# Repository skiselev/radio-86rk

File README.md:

# Radio 86RK
Re-make of the Soviet Ham Radio computer published in Radio Magazine in 1986

## Hardware Documentation

## Table of Content
* [Introduction](#introduction)
* [Specifications](#specifications)
* [Project Notes](#project-notes)
* [Hardware Documentation](#hardware-documentation)
  * [Schematic and PCB Layout](#schematic-and-pcb-layout)
  * [Connectors](#connectors)
  * [Bill of Materials](#bill-of-materials)
  * [Memory Map](#memory-map)
* [Firmware Documentation](#firmware-documentation)
  * [Monitor](#monitor)
* [Release Notes](#release-notes)
  * [Changes](#changes)
  * [Known Issues](#known-issues)

## Introduction
This project is a remake of [Radio-86RK](https://en.wikipedia.org/wiki/Radio-86RK) - a soviet ham radio computer. The original design was published in Radio Magazine, an amateur radio and DIY electronics oriented publication, starting from [April 1986](Radio-86RK_Publications.md). Hence the "Radio" and "86" in the name ("RK" stands for ham radio computer).

The goal of the original design was to create a computer that can be built relatively easily and cheaply using commonly available components. Therefore it included several short-cuts. For example it didn't use 8228 bus controller. Instead, it uses */WR* and *DBIN* CPU signals instead to distinguish between write and read CPU cycles. Since the system doesn't decode I/O control signals, all the I/O devices are memory mapped. Another optimization is the use of DMA controller for both supplying the data to the CRT controller and for refreshing DRAMs. The system didn't support interrupts. The sound was implemented using *INTE* output of the CPU. The software would use **EI**/**DI** instructions to generate sound. There are no graphics capabilities. The font size was limited to 128 characters (8275 CRT controller limitation), and given that it had to support both Latin and Cyrillic ABCs, it only had capital letters for both ABCs. The CRT controller shares 16 MHz clock oscillator with the CPU (not uncommon in other home computers at that time period).

Despite the limitations, the design was fairly successful, many people have built this computer, and there are some that still building one, this project included. In addtion, several factories manufactured computers based on (but not always compatible with) this design - e.g. [Mikrosha](https://oldcomputer.info/8bit/mikrosha/index.htm), [Apogee BK-01](https://ru.wikipedia.org/wiki/%D0%90%D0%BF%D0%BE%D0%B3%D0%B5%D0%B9_%D0%91%D0%9A-01), and a few more.

### Specifications of the Original Design
  * KR580VM80A (Intel 8080) CPU @ 1.78 MHz (16 MHz divided by 9)
  * 16 KiB to 32 KiB DRAM, 2 KiB ROM (monitor software)
  * KR580VG75 (Intel 8275) CRT controller which works together with KR580VT57 (Intel 8257) DMA controller. 1 KiB ROM is used for font
  * Two KR580VV55A (Intel 8255A) PPIs. One is used for keyboard and cassette I/O, another one for the extension port
  * Normally the computer consisted of 2 or 3 PCBs - the mainboard, the keyboard, and the keypad.

### Modifications to the Original Design
 * 16 DRAM ICs replaced with a single 32 KiB SRAM IC
 * Font ROM size increased to 2 KiB, so that it fits an alternative font. CRT controller GPA0 attribute is used to switch between fonts.
 * Reverse video attribute implemented in CRT controller
 * Added 8251 USART and 8253 timer. The timer is used for dividing the clock for USART and for sound generation.
 * Single board design, including an integrated mechanical keyboard
 * The work is largely based on [Radio-86RК-SRAM](http://radio86rk.pbworks.com/w/page/58467718/Radio-86R%D0%9A-SRAM) project created by Alexey Khudyakov (alexcp).

## Specifications
* Processor: Intel 8080A / КР580ВМ80А CPU running at 1.78 MHz
* Memory:
  * RAM: 32 KiB SRAM
  * ROM: 2 KiB UV EPROM with system monitor software
* Video: Intel 8275 / КР580ВГ75 CRT Controller
  * Alphanumeric display
  * 2 KiB UV EPROM with font
  * Composite video output (50 Hz)
* Audio:
  * Intel 8253 / КР580ВИ53 (single channel)
  * CPU INTE output
* Parallel Interface:
  * Intel 8255А / КР580ВВ55А PPI
  * 26-pin expansion header
* Serial Interface:
  * Intel 8251А / КР580ВВ51А USART
  * DE-9 connector
* Built-in 67-keys keyboard
* Cassette recorder interface

## Project Notes

Check [Project Notes](Project_Notes.md) for the information about building this project

## Hardware Documentation

### Documentation for the Previous Versions

* [Version 1.3](https://github.com/skiselev/radio-86rk/tree/v1.3)
* [Version 1.2](https://github.com/skiselev/radio-86rk/tree/v1.2)
* [Version 1.1](https://github.com/skiselev/radio-86rk/tree/v1.1)

### Schematic and PCB Layout

* [Schematic - Version 1.4](KiCad/Radio-86RK-Schematic-1.4.pdf)
* [PCB Layout - Version 1.4](KiCad/Radio-86RK-Board-1.4.pdf)

### Connectors

#### J1 - Composite Video

Pin | Description     
--- | ---------------
Tip (the inner contact) | Output: Composite Video
Ring / Sleeve         |	Power: GND

#### J2 - Power (5V)
Connect regulated +5V power supply to this connector.

Note: The 8080A CPU, clock generator, and serial port transmitters and receivers use +12V/-5V/-12V voltages. An on-board DC-DC converter (U26) is used to obtain these voltages. Instead of using the DC-DC converter it is possible to provide these voltages directly to the system using J3 connector.

Pin | Description     
--- | ---------------
Tip (the inner contact) | Power: 5V (positive terminal)
Barrel / Sleeve         |	Power: GND (negative terminal)

#### J3 - Power (5V, 12V, -12V)
Connect regulated 5V/12V/-12V power supply to this connector.

Pin | Description     
--- | ---------------
1, 2, 3 | Power: GND
4, 5, 6 |	Power: 5V
7   |	Power: 12V
8   |	Power: -12V

#### J4 - Cassette Connector
Pin | Description     
--- | ---------------
1, 2, 3, 8   | Power: GND
4   |	Output: Sound output to cassette recorder (line level)
5   |	Input: Sound input from cassette recorder (line level)
6, 7 |	Not connected

#### J5 - Serial Port Connector
Pin | Description     
--- | ---------------
1   | Not connected: DCD
2   | Input: RX
3   | Output: TX
4   | Output: DTR
5   | Power: GND
6   | Input: DSR
7   | Output: RTS
8   | Input: CTS
9   | Not connected: RI

#### J6 - Parallel Port Connector
Pin | Description | Pin | Description
--- | ----------- | --- | ----------------
1   | Output: PC0 | 2   | Input: PA0
3   | Output: PC1 | 4   | Input: PA1
5   | Output: PC2 | 6   | Input: PA2
7   | Output: PC3 | 8   | Input: PA3
9   | Output: PC4 | 10  | Input: PA4
11  | Output: PC5 | 12  | Input: PA5
13  | Output: PC6 | 14  | Input: PA6
15  | Output: PC7 | 16  | Input: PA7
17  | Output: PB7 | 18  | Output: PB0
19  | Output: PB6 | 20  | Output: PB1
21  | Output: PB5 | 22  | Output: PB2
23  | Output: PB4 | 24  | Output: PB3
25  | Power: +5V  | 26  | Power: GND

### Bill of Materials

* [Radio-86RK project on Mouser.com](https://www.mouser.com/ProjectManager/ProjectDetail.aspx?AccessID=d3d8f92a02) - View and order all components except of the PCB, and most Intel 8xxx ICs.

* [Unicorn Electronics](https://www.unicornelectronics.com/prod.htm) is a good source for Intel 8xxx or compatible ICs, 7400-series TTL ICs, and 74LS00-series TTL-LS ICs

Component type     | Reference | Description                                 | Quantity | Possible sources and notes
------------------ | --------- | ------------------------------------------- | -------- | --------------------------
PCB                |           | Radio-86RK PCB                              | 1        | Buy from my Tindie store: [Radio-86RK - PCB](https://www.tindie.com/products/weird/radio-86rk-pcb/) or order from a PCB manufacturer of your choice using provided Gerber or KiCad files
Capacitor          | C1 - C32  | 0.1 uF, MLCC, 5 mm Pitch                    | 32       | Mouser [594-K104K15X7RF53H5](https://www.mouser.com/ProductDetail/594-K104K15X7RF53H5)
Capacitor          | C33 - C38 | 47 uF, 25V, Electrolytic or Organic Polymer | 6 	      | Mouser [80-A750EK476M1EAAE40](https://www.mouser.com/ProductDetail/80-A750EK476M1EAAE40)
Capacitor          | C39       | 0.22 uF, MLCC, 5 mm Pitch                   | 1        | Mouser [810-FG24X7R1H224KNT0](https://www.mouser.com/ProductDetail/810-FG24X7R1H224KNT0)
Capacitor          | C40       | 22 nF, MLCC, 5 mm Pitch                     | 1        | Mouser [810-FG28X7R1H223KNT0](https://www.mouser.com/ProductDetail/810-FG28X7R1H223KNT0)
Capacitor          | C41       | 10 nF, MLCC, 5 mm Pitch                     | 1        | Mouser [810-FG28X7R1H103KNT0](https://www.mouser.com/ProductDetail/810-FG28X7R1H103KNT0)
Capacitor          | C42       | 2.2 nF, MLCC, 5 mm Pitch                    | 1        | Mouser [810-FG28X7R1H222KNT0](https://www.mouser.com/ProductDetail/810-FG28X7R1H222KNT0)
Capacitor          | C43       | 1 nF, MLCC, 5 mm Pitch                      | 1        | Mouser [810-FG28C0G1H102JNT6](https://www.mouser.com/ProductDetail/810-FG28C0G1H102JNT6)
Capacitor          | C44       | 10 pF, MLCC, 5 mm Pitch                     | 1        | Mouser [810-FG28C0G1H100DNT00](https://www.mouser.com/ProductDetail/810-FG28C0G1H100DNT0)
Diode              | D1 - D9  | 1N4148                                       | 9        | Mouser [512-1N4148](https://www.mouser.com/ProductDetail/512-1N4148)
LED                | D10       | LED Indicator, 3 mm, Green                  | 1        | Mouser [630-HLMP-1503-C0002](https://www.mouser.com/ProductDetail/630-HLMP-1503-C0002)
LED                | D11       | LED Indicator, 3 mm, Yellow                 | 1        | Mouser [630-HLMP-1401](https://www.mouser.com/ProductDetail/630-HLMP-1401)
Polyfuse           | F1        | 1.1A, 5 mm Pitch                            | 1        | Mouser [576-16R110BU](https://www.mouser.com/ProductDetail/576-16R110BU)
Connector          | JP1, JP2  | 4 pin header, 2.54 mm Pitch                 | 2        | Mouser [649-68000-204HLF](https://www.mouser.com/ProductDetail/649-68000-204HLF)
Connector          | JP1, JP2  | Jumper, 2.54 mm Pitch                       | 4        | Mouser [806-SX1100-B)](https://www.mouser.com/ProductDetail/806-SX1100-B)
Connector          | J1        | RCA Phono connector, Yellow                 | 1        | Mouser [490-RCJ-014](https://www.mouser.com/ProductDetail/490-RCJ-014)
Connector          | J2        | DC Power Jack, 2mm                          | 1        | Mouser [806-KLDX-0202-A](https://www.mouser.com/ProductDetail/806-KLDX-0202-A)
Connector          | J3        | 8 pin friction lock connector               | 1        | Mouser [571-6404568](https://www.mouser.com/ProductDetail/571-6404568)
Connector          | J4        | DIN 8-pos, Right Angle, PCB mount           | 1        | Mouser [490-SDF-80J](https://www.mouser.com/ProductDetail/490-SDF-80J)
Connector          | J5        | Sub-D DE9M, Right Angle, PCB mount          | 1        | Mouser [523-L717SDE09P1ACH3R](https://www.mouser.com/ProductDetail/523-L717SDE09P1ACH3R)
Connector          | J6        | 13x2 pin header, shrouded                   | 1        | Mouser [517-30326-6002](https://www.mouser.com/ProductDetail/517-30326-6002)
Connector          | J7        | 20x1 pin socket                             | 1        | Mouser [517-929850-01-20-RB](https://www.mouser.com/ProductDetail/517-929850-01-20-RB). Note: Optional, for extension board connection
Transistor         | Q1, Q2    | 2N3904                                      | 2        | Mouser [512-2N3904TA](https://www.mouser.com/ProductDetail/512-2N3904TA)
Resistor           | R1        | 33 ohm                                      | 1        | Mouser [660-CF1/4CT52R330J](https://www.mouser.com/ProductDetail/660-CF1-4CT52R330J)
Resistor           | R2        | 75 ohm                                      | 1        | Mouser [660-CF1/4CT52R750J](https://www.mouser.com/ProductDetail/660-CF1-4CT52R750J)
Resistor           | R3        | 150 ohm                                     | 1        | Mouser [660-CF1/4CT52R151J](https://www.mouser.com/ProductDetail/660-CF1-4CT52R151J)
Resistor           | R4        | 330 ohm                                     | 1        | Mouser [660-CF1/4CT52R331J](https://www.mouser.com/ProductDetail/660-CF1-4CT52R331J)
Resistor           | R5        | 1.5 k                                       | 1        | Mouser [660-CF1/4CT52R152J](https://www.mouser.com/ProductDetail/660-CF1-4CT52R152J)
Resistor           | R6 - R13  | 1 k                                         | 8        | Mouser [660-CF1/4CT52R102J](https://www.mouser.com/ProductDetail/660-CF1-4CT52R102J)
Resistor           | R14       | 2.4 k                                       | 1        | Mouser [660-CF1/4CT52R242J](https://www.mouser.com/ProductDetail/660-CF1-4CT52R242J)
Resistor           | R15       | 12 k                                        | 1        | Mouser [660-CF1/4CT52R123J](https://www.mouser.com/ProductDetail/660-CF1-4CT52R123J)
Resistor Array     | RN1       | 10 k, SIP10                                 | 1        | Mouser [652-4610X-1LF-10K](https://www.mouser.com/ProductDetail/652-4610X-1LF-10K)
Resistor Array     | RN2 - RN4 | 4.7 k, SIP6                                 | 3        | Mouser [652-4606X-1LF-4.7K](https://www.mouser.com/ProductDetail/652-4606X-1LF-4.7K)
Speaker            | SP1       | 12 mm speaker                               | 1        | Mouser [665-AT-1224TWTR](https://www.mouser.com/ProductDetail/665-AT-1224TWTR)
Keyboard Switch    | SW1 - SW67 | Cherry MX Blue (Clicky)                    | 67       | Mouser [540-MX1A-E1NW](https://www.mouser.com/ProductDetail/540-MX1A-E1NW)
Switch Leveling Kit | SW11, SW64 | Leveling kit for MX 1x2, 1x2.25, 1x2.75   | 2        | Mouser [540-G99-0742](https://www.mouser.com/ProductDetail/540-G99-0742)
Switch Leveling Kit | SW64     | Leveling kit for MX 1x8                     | 1        | Mouser [540-G99-0226](https://www.mouser.com/ProductDetail/540-G99-0226) Note: Use the wire from this part and one of 540-G99-0742 to build a through hole leveling kit for the spacebar
Tactile Switch     | SW68      | 6 mm Tactile Switch Right Angle             | 1        | Mouser [653-B3F-3152](https://www.mouser.com/ProductDetail/653-B3F-3152)
Switch Keycap      | SW68      | 4 x 4 mmm Tactile Switch Key Cap, Orange    | 1        | Mouser [653-B32-1020](https://www.mouser.com/ProductDetail/653-B32-1020)
Integrated Circuit | U1        | Intel 8080A / КР580ВМ80А, CPU               | 1        | Unicorn Electronics [8080A](https://www.unicornelectronics.com/IC/8000.html), Jameco [52046](https://www.jameco.com/z/8080A-Major-Brands-IC-8080A-8-Bit-MOS-MPU_52046.html)
Integrated Circuit | U2        | Intel 8224 / КР580ГФ24, Clock Generator     | 1        | Unicorn Electronics [8224](https://www.unicornelectronics.com/IC/8000.html)
Integrated Circuit | U3        | Intel 8251А / КР580ВВ51А, USART             | 1        | Unicorn Electronics [8251A](https://www.unicornelectronics.com/IC/8000.html)
Integrated Circuit | U4        | Intel 8253 / КР580ВИ53, PIT                 | 1        | Unicorn Electronics [8253](https://www.unicornelectronics.com/IC/8000.html), Mouser [968-CP82C54Z](https://www.mouser.com/ProductDetail/968-CP82C54Z)
Integrated Circuit | U5, U6    | Intel 8255А / КР580ВВ55А, PPI               | 2        | Unicorn Electronics [8055A](https://www.unicornelectronics.com/IC/8000.html), Mouser [968-CP82C55A-5Z](https://www.mouser.com/ProductDetail/968-CP82C55A-5Z), Jameco [52732](https://www.jameco.com/z/8255A-5-Major-Brands-IC-8255A-5-Programmable-Peripheral-Interface-40-pin-DIP_52732.html)
Integrated Circuit | U7        | Intel 8257 / КР580ВТ57, DMA Controller      | 1        | Unicorn Electronics [8257](https://www.unicornelectronics.com/IC/8000.html)
Integrated Circuit | U8        | Intel 8275 / КР580ВГ75, CRT Controller      | 1        | Unicorn Electronics [8275](https://www.unicornelectronics.com/IC/8000.html), Jameco [52821](https://www.jameco.com/z/8275-Major-Brands-Programmable-CRT-Controller-DIP-40_52821.html)
Integrated Circuit | U9        | AS6C62256, SRAM 32Kx8                       | 1        | Mouser [913-AS6C62256-55PCN](https://www.mouser.com/ProductDetail/913-AS6C62256-55PCN), Unicorn Electronics [62256LP](https://www.unicornelectronics.com/IC/STATIC.html)
Integrated Circuit | U10, U11  | 2716 / КР573РФ5, 2Kx8 EPROM                 | 2        | Mouser [556-AT28C64B15PU](https://www.mouser.com/ProductDetail/556-AT28C64B15PU), Unicorn Electronics [2716](https://www.unicornelectronics.com/IC/EPROM.html). Note: 2716, 2732, 2764, 27C64 EPROMs, or 28C64 EEPROMs can be used
Integrated Circuit | U12       | 74LS373/К555ИР22, 8-bit Latch, 3-state outputs | 1     | Mouser [595-SN74LS373N](https://www.mouser.com/ProductDetail/595-SN74LS373N)
Integrated Circuit | U13       | 74198/К155ИР13, 8-bit Shift Register        | 1        | Unicorn Electronics [74198](https://www.unicornelectronics.com/IC/7400.html)
Integrated Circuit | U14       | 74LS138/К555ИД7, Decoder 3 to 8 active low outputs | 1 | Mouser [595-SN74LS138N](https://www.mouser.com/ProductDetail/595-SN74LS138N), Unicorn Electronics [74LS138](https://www.unicornelectronics.com/IC/74LS.html)
Integrated Circuit | U15       | 7492/К155ИЕ4, Divide by 12 counter          | 1        | Mouser [595-SN74LS92N](https://www.mouser.com/ProductDetail/595-SN74LS92N), Unicorn Electronics [74LS92](https://www.unicornelectronics.com/IC/74LS.html)
Integrated Circuit | U16       | 7486/К155ЛП5, Quad 2-input XOR              | 1        | Mouser [595-SN74LS86AN](https://www.mouser.com/ProductDetail/595-SN74LS86AN), Unicorn Electronics [74LS86](https://www.unicornelectronics.com/IC/74LS.html)
Integrated Circuit | U17       | 7474/К155ТМ2, Dual D Flip-flop, Set & Reset | 1        | Mouser [595-SN74LS74AN](https://www.mouser.com/ProductDetail/595-SN74LS74AN), Unicorn Electronics [74LS74](https://www.unicornelectronics.com/IC/74LS.html)
Integrated Circuit | U18       | 7408/К155ЛИ1, Quad 2-input AND              | 1        | Mouser [595-SN74LS08N](https://www.mouser.com/ProductDetail/595-SN74LS08N), Unicorn Electronics [74LS08](https://www.unicornelectronics.com/IC/74LS.html)
Integrated Circuit | U19       | 7404/К155ЛН1, Hex Inverter                  | 1        | Mouser [595-SN74LS04N](https://www.mouser.com/ProductDetail/595-SN74LS04N), Unicorn Electronics [74LS04](https://www.unicornelectronics.com/IC/74LS.html)
Integrated Circuit | U20       | 7400/К155ЛА3, Quad 2-input NAND             | 1        | Mouser [595-SN74LS00N](https://www.mouser.com/ProductDetail/595-SN74LS00N), Unicorn Electronics [74LS00](https://www.unicornelectronics.com/IC/74LS.html)
Integrated Circuit | U21       | TL071/К140УД6, Operational Amplifier        | 1        | Mouser [595-TL071IP](https://www.mouser.com/ProductDetail/595-TL071IP)
Integrated Circuit | U22       | SN75154N/К170УП2В, Quad RS-232 Receiver     | 1        | Mouser [595-SN75154N](https://www.mouser.com/ProductDetail/595-SN75154N), Unicorn Electronics [75154](https://www.unicornelectronics.com/IC/INTERFACE.html)
Integrated Circuit | U23, U24  | SN75150P/К170АП2, Dual RS-232 Driver        | 2        | Mouser [595-SN75150P](https://www.mouser.com/ProductDetail/595-SN75150P), Unicorn Electronics [75150](https://www.unicornelectronics.com/IC/INTERFACE.html)
Integrated Circuit | U25       | LM7905/КР1179ЕНВ, Negative 5V 1A Linear Regulator | 1  | Mouser [926-LM7905CT-NOPB](https://www.mouser.com/ProductDetail/926-LM7905CT-NOPB), Unicorn Electronics [7905T](https://www.unicornelectronics.com/IC/VOLT.html)
DC-DC Converter    | U26       | IZ0512, +/-12V +/-125mA, 4.5V-9V input      | 1        | Mouser [209-IZ0512S](https://www.mouser.com/ProductDetail/209-IZ0512S)
Integrated Circuit | U27       | DS1233-5, CPU Supervisory Circuit           | 1        | Mouser [700-DS1233-5T&R](https://www.mouser.com/ProductDetail/700-DS1233-5TR)
Crystal            | Y1        | 16 MHz, Series, HC-49U                      | 1        | Mouser [774-ATS160-E](https://www.mouser.com/ProductDetail/774-ATS160-E)
IC Socket          | U1, U5, U6, U7, U8 | 40 pin DIP                         | 5        | Mouser [649-DILB40P223TLF](https://www.mouser.com/ProductDetail/649-DILB40P223TLF), [517-4840-6000-CP](https://www.mouser.com/ProductDetail/517-4840-6000-CP)
IC Socket          | U3, U9, U10, U11    | 28 pin DIP                                  | 4        | Mouser [649-DILB28P223TLF](https://www.mouser.com/ProductDetail/649-DILB28P223TLF), [517-4828-6000-CP](https://www.mouser.com/ProductDetail/517-4828-6000-CP)
IC Socket          | U4, U13   | 24 pin DIP                          | 2        | Mouser [649-DILB24P-223TLF](https://www.mouser.com/ProductDetail/649-DILB24P-223TLF), [517-4824-6000-CP](https://www.mouser.com/ProductDetail/517-4824-6000-CP)
IC Socket          | U12       | 20 pin DIP                                  | 1        | Mouser [649-DILB20P-223TLF](https://www.mouser.com/ProductDetail/649-DILB20P-223TLF), [517-4820-3000-CP](https://www.mouser.com/ProductDetail/517-4820-3000-CP)
IC Socket          | U2, U14, U22 | 16 pin DIP                               | 3        | Mouser [649-DILB16P-223TLF](https://www.mouser.com/ProductDetail/649-DILB16P-223TLF), [517-4816-3000-CP](https://www.mouser.com/ProductDetail/517-4816-3000-CP)
IC Socket          | U15 - U20 | 14 pin DIP                                  | 6        | Mouser [649-DILB14P-223TLF](https://www.mouser.com/ProductDetail/649-DILB14P-223TLF), [517-4814-3000-CP](https://www.mouser.com/ProductDetail/517-4814-3000-CP)
IC Socket          | U21, U23, U24 | 8 pin DIP                               | 3        | Mouser [649-DILB8P223TLF](https://www.mouser.com/ProductDetail/649-DILB8P223TLF), [517-4808-3000-CP](https://www.mouser.com/ProductDetail/517-4808-3000-CP)

### Memory Map
* 0000h - 7FFFh - SRAM
  * 7600h - 7FFFh - Display buffer and monitor variables
* 8000h - 8FFFh - 8255A PPI (Keyboard, Cassette recorder, Sound control)
  * 8000h - Channel A data
  * 8001h - Channel B data
  * 8002h - Channel C data
  * 8003h - Control word
* 9000h - 9FFFh - 8253 Timer (USART Clock, Sound)
  * 9000h - Channel 0 count
  * 9001h - Channel 1 count
  * 9002h - Channel 2 count
  * 9003h - Control word
* 0A000h - 0AFFFh - 8255A PPI (Parallel Interface)
  * 0A000h - Channel A data
  * 0A001h - Channel B data
  * 0A002h - Channel C data
  * 0A003h - Control word
* 0B000h - 0BFFFh - 8251A USART
  * 0B000h - Data register
  * 0B001h - Command register
* 0C000h - 0CFFFh - 8275 CRT Controller
* 0D000h - 0DFFFh - Unused
* 0E000h - 0EFFFh - 8257 DMA Controller (write only)
* 0E000h - 0FFFFh - Monitor EPROM (read only)

## Firmware Documentation

### Monitor

#### Monitor Commands
* Memory Operations
  * **D\<Start_Address\>,\<End_Address\>** - Display memory content in hexadecimal
  * **L\<Start_Address\>,\<End_Address\>** - Display memory content in ASCII
  * **F\<Start_Address\>,\<End_Address\>,\<Value\>** - Fill memory with the specified value
  * **M\<Address\>** - Modify memory content
  * **T\<Start_Address\>,\<End_Address\>,\<Destination_Start_Address\>** - Copy memory block to destination
  * **C\<Start_Address\>,\<End_Address\>,\<Destination_Start_Address\>** - Compare memory block with destination
  * **S\<Start_Address\>,\<End_Address\>,\<Value\>** - Search memory for a value
  * **R\<ROM_Start_Address\>,\<ROM_End_Address\>,\<Destination_Start_Address\>** - Read from the ROM connected to the Parallel interface to memory
* Run Control
  * **G\<Start_Address\>\[,End_Address\]** - Run code, optionally stop at the specified address
  * **X** - Display and modify registers
* Cassette Input/Output
  * **O\<Start_Address\>,\<End_Address\>\[,Speed\]** - Write memory to cassette. Default speed is 1Dh / 1200 bps
  * **I\[Offset\]\[,Speed\]** - Read data from to cassette memory at specified offset

#### Monitor Subroutines:
* 0F803h - Keyboard input
  * Input: None
  * Output: A - character code read from keyboard
* 0F806h - Cassette input
  * Input: A=0FFh - with sync; A=08h - no sync
  * Output: A - data read from cassette
* 0F809h - Print character to screen
  * Input: C - character to print
* 0F80Ch - Cassette output
  * Input: C - data to write
* 0F812h - Query keyboard
  * Output: A=00h - key not pressed; A=0FFh - key pressed
* 0F815h - Print to screen in hex
  * Input: A - data to print
* 0F818h - Print string
  * Input: HL - string address
* 0F81Bh - Get key
  * Output: A=0FFh - key not pressed; A=0FEh - Rus/Lat; otherwise A - key code
* 0F81Eh - Get cursor position
  * Output: H - row, L - column
* 0F821h - Read character from screen at current cursor position
  * Output: A - char read from screen
* 0F824h - Read from cassette
  * Input: HL - offset of memory buffer to store data to
  * Output: HL - start; DE - end; BC - checksum

## Release Notes

### Changes
* Version 1.4
  * Change keyboard layout to QWERTY
  * Add the J7 extension connector
  * Add support for 2732, 2764 and 27C64 EPROMs and 28C64 EEPROM.

* Version 1.3
  * Fix issues from version 1.1 and version 1.2:
    * Use key labels "Ь X" and "СС SHIFT" on top silkscreen
    * Video signal generation circuit: use R2 = 75 Ohm and R5 = 1.5 kOhm
    
* Version 1.2
  * Add F5 key
  * Add copyright year on the top silkscreen

* Version 1.1
  * Fix all known issues of version 1.0
  * Use DS1233-5 mircoprocessor supervisor to generate reset signal
  * Implement reverse video attribute

* Version 1.0
  * Initial version

### Known Issues
* Version 1.3
  * No known issues

* Version 1.2
  * Top silkscreen: "Ь" and "X" key labels are swapped
  * Top silkscreen: More correct translation for "СС" is "SHIFT"
  * Video signal generation: Produced video Vpp and the backporch levels are a bit too high. Use R2 = 75 to 100 Ohm, and R5 = 1.5 kOhm for proper video signal levels (Reported by Martin Lukasek)
* Version 1.1
  * Top silkscreen: "Ь" and "X" key labels are swapped
  * Top silkscreen: More correct translation for "СС" is "SHIFT"
  * Top silkscreen: No copyright year
  * Video signal generation: Produced video Vpp and the backporch levels are a bit too high. Use R2 = 75 to 100 Ohm, and R5 = 1.5 kOhm for proper video signal levels (Reported by Martin Lukasek)

* Version 1.0
  * 8224 (U2) should use DIP-16 footprint
  * Down and Right buttons swapped
  * Reset RC does not provide enough time for the system to properly reset at power-on

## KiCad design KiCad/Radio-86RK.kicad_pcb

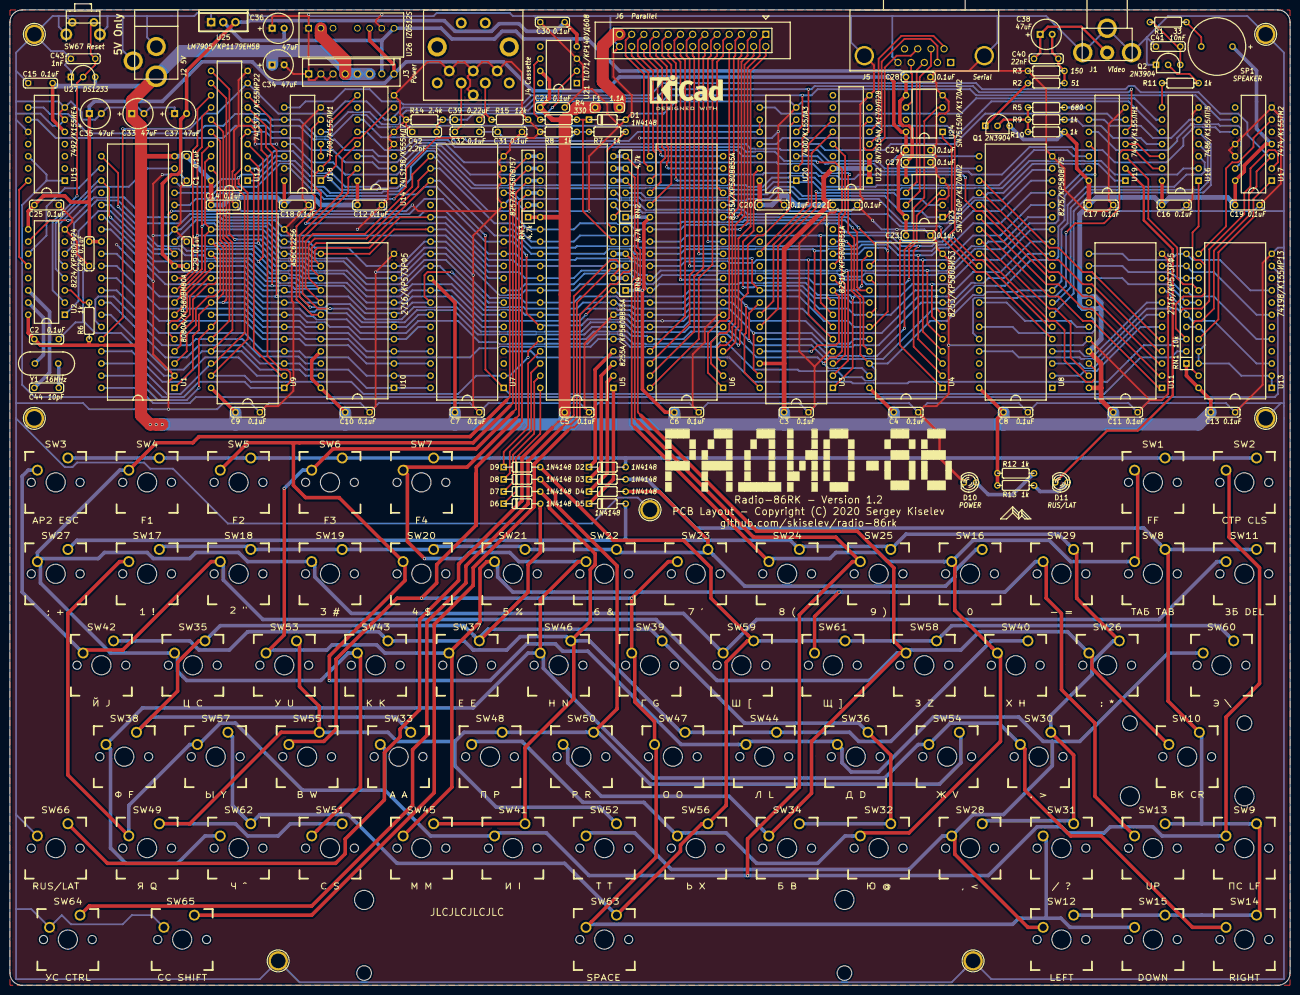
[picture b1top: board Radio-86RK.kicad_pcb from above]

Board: 2 copper layers, 266.7 x 203.2 mm, 186 parts (0 on the bottom side), 194 nets.

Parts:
C1, C2, C3, C4, C5, C6, C7, C8, C9, C10, C11, C12, C13, C14, C15, C16, C17, C18, C19, C20, C21, C22, C23, C24, C25, C26, C27, C28, C29, C30, C31, C32: 0.1uF; Cap_Cer_508
C33, C34, C35, C36, C37, C38: 47uF; Cap_Elec_Radial_6.3mm
C39: 0.22uF; Cap_Cer_508
C40: 22nF; Cap_Cer_508
C41: 10nF; Cap_Cer_508
C42: 2.2nF; Cap_Cer_508
C43: 1nF; Cap_Cer_508
C44: 10pF; Cap_Cer_508
D1, D2, D3, D4, D5, D6, D7, D8, D9: 1N4148; Diode_762
D10: POWER; LED_3mm
D11: RUS/LAT; LED_3mm
F1: 1.1A; Cap_Cer_508
HOLE1, HOLE2, HOLE3, HOLE4, HOLE5, HOLE6, HOLE7: M3; Hole_3mm
J1: Video; Conn_RCA_Right
J2: 5V; Conn_Power_Jack_Circular_Pads
J3: Power; Conn_Friction_Lock_8P_2.54mm
J4: Cassette; Conn_DIN_8pin
J5: Serial; Conn_Dsub_DE9M
J6: Parallel; Conn_Pin_Header_13x2_2.54mm_Shrouded
Q1, Q2: 2N3904; Transistor_TO92_EBC_254
R1: 33; Res_762
R2: 51; Res_762
R3: 150; Res_762
R4: 330; Res_762
R5: 680; Res_762
R6, R7, R8, R9, R10, R11, R12, R13: 1k; Res_762
R14: 2.4k; Res_762
R15: 12k; Res_762
RN1: 10k; Conn_SIL10
RN2, RN3, RN4: 4.7k; Conn_SIL6
SP1: SPEAKER; Speaker_12mm
SW1: FF; CHERRY_PCB_100H
SW2: СТР CLS; CHERRY_PCB_100H
SW3: АР2 ESC; CHERRY_PCB_100H
SW4: F1; CHERRY_PCB_100H
SW5: F2; CHERRY_PCB_100H
SW6: F3; CHERRY_PCB_100H
SW7: F4; CHERRY_PCB_100H
SW8: ТАБ TAB; CHERRY_PCB_100H
SW9: ПС LF; CHERRY_PCB_100H
SW10: ВК CR; CHERRY_PCB_225H
SW11: ЗБ DEL; CHERRY_PCB_100H
SW12: LEFT; CHERRY_PCB_100H
SW13: UP; CHERRY_PCB_100H
SW14: RIGHT; CHERRY_PCB_100H
SW15: DOWN; CHERRY_PCB_100H
SW16: 0; CHERRY_PCB_100H
SW17: 1 !; CHERRY_PCB_100H
SW18: 2 "; CHERRY_PCB_100H
SW19: 3 #; CHERRY_PCB_100H
SW20: 4 $; CHERRY_PCB_100H
SW21: 5 %; CHERRY_PCB_100H
SW22: 6 &; CHERRY_PCB_100H
SW23: 7 '; CHERRY_PCB_100H
SW24: 8 (; CHERRY_PCB_100H
SW25: 9 ); CHERRY_PCB_100H
SW26: : *; CHERRY_PCB_100H
SW27: ; +; CHERRY_PCB_100H
SW28: , <; CHERRY_PCB_100H
SW29: - =; CHERRY_PCB_100H
SW30: . >; CHERRY_PCB_100H
SW31: / ?; CHERRY_PCB_100H
SW32: Ю @; CHERRY_PCB_100H
SW33: А A; CHERRY_PCB_100H
SW34: Б B; CHERRY_PCB_100H
SW35: Ц C; CHERRY_PCB_100H
SW36: Д D; CHERRY_PCB_100H
SW37: Е E; CHERRY_PCB_100H
SW38: Ф F; CHERRY_PCB_100H
SW39: Г G; CHERRY_PCB_100H
SW40: Х H; CHERRY_PCB_100H
SW41: И I; CHERRY_PCB_100H
SW42: Й J; CHERRY_PCB_100H
SW43: К K; CHERRY_PCB_100H
SW44: Л L; CHERRY_PCB_100H
SW45: М M; CHERRY_PCB_100H
SW46: Н N; CHERRY_PCB_100H
SW47: О O; CHERRY_PCB_100H
SW48: П P; CHERRY_PCB_100H
SW49: Я Q; CHERRY_PCB_100H
SW50: Р R; CHERRY_PCB_100H
SW51: С S; CHERRY_PCB_100H
SW52: Т T; CHERRY_PCB_100H
SW53: У U; CHERRY_PCB_100H
SW54: Ж V; CHERRY_PCB_100H
SW55: В W; CHERRY_PCB_100H
SW56: Ь X; CHERRY_PCB_100H
SW57: Ы Y; CHERRY_PCB_100H
SW58: З Z; CHERRY_PCB_100H
SW59: Ш [; CHERRY_PCB_100H
SW60: Э \; CHERRY_PCB_150H
SW61: Щ ]; CHERRY_PCB_100H
SW62: Ч ^; CHERRY_PCB_100H
SW63: SPACE; CHERRY_PCB_625H
SW64: УС CTRL; CHERRY_PCB_125H
SW65: CC SHIFT; CHERRY_PCB_125H
SW66: RUS/LAT; CHERRY_PCB_100H
SW67: Reset; Switch_Tactile_6mm_Right
U1: 8080A/КР580ВМ80А; IC_DIP40_600
U2: 8224/КР580ГФ24; IC_DIP16_300
U3: 8251A/КР580ВВ51А; IC_DIP28_600
U4: 8253/КР580ВИ53; IC_DIP24_600
U5, U6: 8255A/КР580ВВ55А; IC_DIP40_600
U7: 8257/КР580ВТ57; IC_DIP40_600
U8: 8275/КР580ВГ75; IC_DIP40_600
U9: AS6C62256; IC_DIP28_600
U10, U11: 2716/КР573РФ5; IC_DIP24_600
U12: 74LS373/К555ИР22; IC_DIP20_300
U13: 74198/К155ИР13; IC_DIP24_600
U14: 74LS138/К555ИД7; IC_DIP16_300
U15: 7492/К155ИЕ4; IC_DIP14_300
U16: 7486/К155ЛП5; IC_DIP14_300
U17: 7474/К155ТМ2; IC_DIP14_300
U18: 7408/К155ЛИ1; IC_DIP14_300
U19: 7404/К155ЛН1; IC_DIP14_300
U20: 7400/К155ЛА3; IC_DIP14_300
U21: TL071/КР140УД608; IC_DIP8_300
U22: SN75154N/К170УП2В; IC_DIP16_300
U23, U24: SN75150P/К170АП2; IC_DIP8_300
U25: LM7905/КР1179ЕН5В; IC_TO220-3_Vert
U26: IZ0512S; DC-DC_SIP8
U27: DS1233; Transistor_TO92_EBC_254
Y1: 16MHz; Crystal_HC-49U_Vert

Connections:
+12V: C23.1, C24.1, C25.1, C26.1, C35.1, J3.8, U1.28, U2.9, U23.8, U24.8, U26.6
-5V: C29.2, C30.2, C37.2, U1.11, U21.4, U25.3
-12V: C27.2, C28.2, C36.2, J3.7, U23.5, U24.5, U25.2, U26.8
/A15: U1.36, U12.9, U14.6, U19.5, U20.2
/DACK: U7.14, U8.6
/DBIN: U1.17, U16.2, U20.1
/DRQ: U7.17, U8.5
/HLDA: U1.21, U7.7
/HOLD: U1.13, U7.10
/INTE: U1.16, U20.9, U20.10
/Input_Output/CTS: J5.8, U22.6
/Input_Output/DSR: J5.6, U22.5
/Input_Output/DTR: J5.4, U24.6
/Input_Output/PA0: J6.2, U6.4
/Input_Output/PA1: J6.4, U6.3
/Input_Output/PA2: J6.6, U6.2
/Input_Output/PA3: J6.8, U6.1
/Input_Output/PA4: J6.10, U6.40
/Input_Output/PA5: J6.12, U6.39
/Input_Output/PA6: J6.14, U6.38
/Input_Output/PA7: J6.16, U6.37
/Input_Output/PB0: J6.18, U6.18
/Input_Output/PB1: J6.20, U6.19
/Input_Output/PB2: J6.22, U6.20
/Input_Output/PB3: J6.24, U6.21
/Input_Output/PB4: J6.23, U6.22
/Input_Output/PB5: J6.21, U6.23
/Input_Output/PB6: J6.19, U6.24
/Input_Output/PB7: J6.17, U6.25
/Input_Output/PC0: J6.1, U6.14
/Input_Output/PC1: J6.3, U6.15
/Input_Output/PC2: J6.5, U6.16
/Input_Output/PC3: J6.7, U6.17
/Input_Output/PC4: J6.9, U6.13
/Input_Output/PC5: J6.11, U6.12
/Input_Output/PC6: J6.13, U6.11
/Input_Output/PC7: J6.15, U6.10
/Input_Output/PVCC: F1.2, J6.25
/Input_Output/RTS: J5.7, U23.7
/Input_Output/RX: J5.2, U22.4
/Input_Output/RXD: U3.3, U22.13
/Input_Output/SPKR: U4.17, U20.13
/Input_Output/TX: J5.3, U23.6
/Input_Output/TXD: U3.19, U23.3
/Input_Output/UART_CLK: U3.9, U3.25, U4.13
/Input_Output/~CTS: U3.17, U22.11
/Input_Output/~DSR: U3.22, U22.12
/Input_Output/~DTR: U3.24, U24.3
/Input_Output/~RTS: U3.23, U23.2
/Keyboard/CTRL: RN4.3, SW64.1, U5.11
/Keyboard/D10+: D10.2, R12.2
/Keyboard/D11+: D11.2, R13.2
/Keyboard/GRAPH: RN4.4, SW65.1, U5.12
/Keyboard/K_PA0: D2.1, U5.4
/Keyboard/K_PA1: D3.1, U5.3
/Keyboard/K_PA2: D4.1, U5.2
/Keyboard/K_PA3: D5.1, U5.1
/Keyboard/K_PA4: D6.1, U5.40
/Keyboard/K_PA5: D7.1, U5.39
/Keyboard/K_PA6: D8.1, U5.38
/Keyboard/K_PA7: D9.1, U5.37
/Keyboard/K_PB0: RN2.4, SW1.2, SW8.2, SW16.2, SW24.2, SW32.2, SW40.2, SW48.2, SW56.2, U5.18
/Keyboard/K_PB1: RN2.5, SW2.2, SW9.2, SW17.2, SW25.2, SW33.2, SW41.2, SW49.2, SW57.2, U5.19
/Keyboard/K_PB2: RN2.6, SW3.2, SW10.2, SW18.2, SW26.2, SW34.2, SW42.2, SW50.2, SW58.2, U5.20
/Keyboard/K_PB3: RN3.6, SW4.2, SW11.2, SW19.2, SW27.2, SW35.2, SW43.2, SW51.2, SW59.2, U5.21
/Keyboard/K_PB4: RN3.5, SW5.2, SW12.2, SW20.2, SW28.2, SW36.2, SW44.2, SW52.2, SW60.2, U5.22
/Keyboard/K_PB5: RN3.4, SW6.2, SW13.2, SW21.2, SW29.2, SW37.2, SW45.2, SW53.2, SW61.2, U5.23
/Keyboard/K_PB6: RN3.3, SW7.2, SW14.2, SW22.2, SW30.2, SW38.2, SW46.2, SW54.2, SW62.2, U5.24
/Keyboard/K_PB7: RN3.2, SW15.2, SW23.2, SW31.2, SW39.2, SW47.2, SW55.2, SW63.2, U5.25
/Keyboard/ROW0: D2.2, SW1.1, SW2.1, SW3.1, SW4.1, SW5.1, SW6.1, SW7.1
/Keyboard/ROW1: D3.2, SW8.1, SW9.1, SW10.1, SW11.1, SW12.1, SW13.1, SW14.1, SW15.1
/Keyboard/ROW2: D4.2, SW16.1, SW17.1, SW18.1, SW19.1, SW20.1, SW21.1, SW22.1, SW23.1
/Keyboard/ROW3: D5.2, SW24.1, SW25.1, SW26.1, SW27.1, SW28.1, SW29.1, SW30.1, SW31.1
/Keyboard/ROW4: D6.2, SW32.1, SW33.1, SW34.1, SW35.1, SW36.1, SW37.1, SW38.1, SW39.1
/Keyboard/ROW5: D7.2, SW40.1, SW41.1, SW42.1, SW43.1, SW44.1, SW45.1, SW46.1, SW47.1
/Keyboard/ROW6: D8.2, SW48.1, SW49.1, SW50.1, SW51.1, SW52.1, SW53.1, SW54.1, SW55.1
/Keyboard/ROW7: D9.2, SW56.1, SW57.1, SW58.1, SW59.1, SW60.1, SW61.1, SW62.1, SW63.1
/Keyboard/RUS_LAT: RN4.2, SW66.1, U5.10
/Keyboard/RUS_LAT_LED: U5.17, U19.1
/Keyboard/TAPE_IN: D1.1, R4.1, U5.13
/Keyboard/TAPE_OUT: R7.2, U5.14
/Keyboard/~RUS_LAT_LED: D11.1, U19.2
/READY: U1.23, U2.4, U7.6
/~CRT_CS: U8.22, U14.11
/~CRT_WR: U8.10, U18.11
/~DMA_CS: U7.11, U14.9, U18.2
/~PIT_CS: U4.21, U14.14
/~PPI1_CS: U5.6, U14.15
/~PPI2_CS: U6.6, U14.13
/~RAM_CS: U9.20, U20.6
/~ROM_CS: U10.18, U18.6
/~UART_CS: U3.11, U14.12
A0: U1.25, U3.12, U4.19, U5.9, U6.9, U7.32, U8.21, U9.10, U10.8
A1: U1.26, U4.20, U5.8, U6.8, U7.33, U9.9, U10.7
A2: U1.27, U7.34, U9.8, U10.6
A3: U1.29, U7.35, U9.7, U10.5
A4: U1.30, U7.37, U9.6, U10.4
A5: U1.31, U7.38, U9.5, U10.3
A6: U1.32, U7.39, U9.4, U10.2
A7: U1.33, U7.40, U9.3, U10.1
A8: U1.34, U9.25, U10.23, U12.12
A9: U1.35, U9.24, U10.22, U12.15
A10: U1.1, U9.21, U10.19, U12.16
A11: U1.40, U9.23, U12.19
A12: U1.37, U9.2, U12.2, U14.1
A13: U1.38, U9.26, U12.5, U14.2
A14: U1.39, U9.1, U12.6, U14.3
D0: U1.10, U3.27, U4.8, U5.34, U6.34, U7.30, U8.12, U9.11, U10.9, U12.13
D1: U1.9, U3.28, U4.7, U5.33, U6.33, U7.29, U8.13, U9.12, U10.10, U12.14
D2: U1.8, U3.1, U4.6, U5.32, U6.32, U7.28, U8.14, U9.13, U10.11, U12.17
D3: U1.7, U3.2, U4.5, U5.31, U6.31, U7.27, U8.15, U9.15, U10.13, U12.18
D4: U1.3, U3.5, U4.4, U5.30, U6.30, U7.26, U8.16, U9.16, U10.14, U12.3
D5: U1.4, U3.6, U4.3, U5.29, U6.29, U7.23, U8.17, U9.17, U10.15, U12.4
D6: U1.5, U3.7, U4.2, U5.28, U6.28, U7.22, U8.18, U9.18, U10.16, U12.7
D7: U1.6, U3.8, U4.1, U5.27, U6.27, U7.21, U8.19, U9.19, U10.17, U12.8
GND: C1.2, C2.2, C3.2, C4.2, C5.2, C6.2, C7.2, C8.2, C9.2, C10.2, C11.2, C12.2, C13.2, C14.2, C15.2, C16.2, C17.2, C18.2, C19.2, C20.2, C21.2, C22.2, C23.2, C24.2, C25.2, C26.2, C27.1, C28.1, C29.1, C30.1, C31.1, C33.2, C34.2, C35.2, C36.1, C37.1, C41.2, C42.2, C43.2, D1.2, D10.1, HOLE1.1, HOLE2.1, HOLE3.1, HOLE4.1, HOLE5.1, HOLE6.1, HOLE7.1, J1.2, J2.2, J2.3, J3.1, J3.2, J3.3, J4.1, J4.2, J4.3, J4.8, J5.5, J5.GND, J6.26, Q2.1, R3.2, R8.2, R14.2, R15.2, SW64.2, SW65.2, SW66.2, SW67.2, SW67.GND, U1.2, U1.14, U2.8, U3.4, U4.12, U5.7, U6.7, U7.16, U7.18, U7.19, U7.20, U8.20, U9.14, U10.12, U11.12, U11.20, U12.10, U13.12, U14.4, U14.5, U14.8, U15.6, U15.7, U15.10, U16.7, U17.7, U17.11, U17.12, U18.7, U19.7, U20.7, U21.3, U22.8, U23.4, U24.4, U25.1, U26.1, U26.7, U27.1
unnamed: C31.2, C32.2, R7.1, R8.1
unnamed: C32.1, J4.4
unnamed: C38.1, C40.2, J1.1
unnamed: C38.2, C40.1, R2.2, R3.1
unnamed: C39.1, J4.5, R15.1
unnamed: C39.2, C42.1, R14.1, U21.2
unnamed: C41.1, Q2.3, R1.1
unnamed: C43.1, SW67.1, U2.2, U27.2
unnamed: C44.1, U2.14
unnamed: C44.2, Y1.1
unnamed: Q1.1, R2.1
unnamed: Q1.2, R5.1, R9.1, R10.2
unnamed: Q2.2, R11.2
unnamed: R1.2, SP1.1
unnamed: R4.2, U21.6
unnamed: R5.2, U19.8
unnamed: R6.1, U2.3
unnamed: R9.2, U16.11
unnamed: R11.1, U16.8
unnamed: RN1.4, U13.1, U13.2, U13.19, U13.21, U13.22
unnamed: RN1.5, U11.9, U13.3
unnamed: RN1.6, U11.15, U13.17
unnamed: RN1.7, U11.10, U13.5
unnamed: RN1.8, U11.14, U13.15
unnamed: RN1.9, U11.11, U13.7
unnamed: RN1.10, U11.13, U13.9
unnamed: U1.15, U2.10
unnamed: U1.19, U2.5
unnamed: U1.22, U2.11
unnamed: U2.15, Y1.2
unnamed: U8.27, U11.1
unnamed: U8.26, U11.2
unnamed: U8.25, U11.3
unnamed: U8.24, U11.4
unnamed: U8.23, U11.5
unnamed: U8.2, U11.6
unnamed: U8.3, U11.7
unnamed: U8.4, U11.8
unnamed: U8.35, U11.18
unnamed: U8.33, U11.19
unnamed: U8.29, U11.22
unnamed: U8.28, U11.23
unnamed: U12.1, U19.12
unnamed: U7.8, U12.11
unnamed: U13.11, U15.1, U15.12
unnamed: U13.13, U17.6
unnamed: U13.16, U19.3
unnamed: U13.20, U17.1
unnamed: U13.23, U17.3, U18.8
unnamed: U14.7, U18.1
unnamed: U8.30, U15.8, U18.9
unnamed: U15.9, U18.10
unnamed: U8.8, U16.4
unnamed: U8.7, U16.5
unnamed: U16.6, U19.9
unnamed: U16.9, U20.8
unnamed: U16.10, U20.11
unnamed: U16.12, U19.4
unnamed: U8.36, U16.13
unnamed: U8.37, U17.2
unnamed: U17.9, U18.5, U20.5
unnamed: U17.10, U20.3
unnamed: U17.13, U19.10
unnamed: U18.3, U18.4
unnamed: U19.6, U20.4
unnamed: U7.9, U19.13
OSC: U2.12, U15.14
PIT2_ENA: U4.16, U5.16
PIT_PLUP: RN2.2, U4.11, U4.14
RESET: U1.12, U2.1, U3.21, U5.35, U6.35, U7.13, U19.11
SER_PLUP: RN2.3, U23.1, U24.1
SPKR_ENA: U5.15, U20.12
TTL_CLK: U2.6, U3.20, U4.9, U4.15, U4.18, U7.12
VCC: C1.1, C2.1, C3.1, C4.1, C5.1, C6.1, C7.1, C8.1, C9.1, C10.1, C11.1, C12.1, C13.1, C14.1, C15.1, C16.1, C17.1, C18.1, C19.1, C20.1, C21.1, C22.1, C33.1, C34.1, F1.1, J2.1, J3.4, J3.5, J3.6, Q1.3, R6.2, R10.1, R12.1, R13.1, RN1.1, RN2.1, RN3.1, RN4.1, SP1.2, U1.20, U2.16, U3.26, U4.24, U5.26, U6.26, U7.31, U8.40, U9.28, U10.21, U10.24, U11.21, U11.24, U12.20, U13.24, U14.16, U15.5, U16.14, U17.4, U17.14, U18.14, U19.14, U20.14, U21.7, U22.1, U22.2, U22.3, U22.15, U26.2, U27.3
~IOR: RN1.2, U7.1, U18.13
~MEMW: RN1.3, U7.4, U16.1
~RD: U3.13, U4.22, U5.5, U6.5, U8.9, U9.22, U10.20, U16.3
~WR: U1.18, U3.10, U4.23, U5.36, U6.36, U7.2, U9.27, U18.12

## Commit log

2020-01-26 README: Initial version, Bill of Materials
2020-01-26 README: Fix cut and paste error
2020-01-28 README: Add Mouser part numbers and links (1)
2020-01-28 README: Add Mouser part numbers and links (2)
2020-01-29 Add KiCad and Gerber files for v1.0
2020-02-21 Change 8224 package to DIP16; Swap Down/Right keys; Fix U21 soviet designation
2020-02-21 Fill zones on the PCB
2020-02-21 Use DS1233 for reset
2020-02-22 Implement inverse video
2020-02-25 Update C44 link
2020-02-28 Add photo of Rdio-86RK with keycaps
2020-02-28 README: Expand hardware specifications; Add Changes and Known Issues
2020-02-28 README: Populate Memory Map and Monitor sections
2020-02-28 Typo fix
2020-02-28 Fix formatting
2020-02-28 Put Changes and Known Issues under Release Notes
2020-02-28 README: Introduction
2020-02-28 Fix issues on the front silkscreen
2020-03-05 Minor silkscreen update: Move U2 value
2020-04-13 README: Add a comment about video output level correction
2022-05-13 README: Update R2 and R5 values
2022-05-13 add files for v1.2
2022-05-13 Updates for version v1.3: Update silkscreen and resistors values in video generation circuit
2022-06-14 Multiple part numbers updates
2022-06-14 README: Update resistors and resistor arrays part numbers
2022-06-14 Add Documentation files
2022-06-15 move pdf files to Documentation
2022-06-15 Add Radio Magazine publications about Radio-86RK
2022-06-15 Add table of content
2022-06-16 Update photo to 1.1 version
2022-06-16 Update README photo to 1.1 version
2022-10-12 Add source files and source binaries for the ROM cartridge
2022-10-12 Update rom_loader.asm code
2024-01-09 Add Version 1.4 files

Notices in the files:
KiCad/Radio-86RK.kicad_pcb:
PCB Layout - Copyright (C) 2020 Sergey Kiselev
